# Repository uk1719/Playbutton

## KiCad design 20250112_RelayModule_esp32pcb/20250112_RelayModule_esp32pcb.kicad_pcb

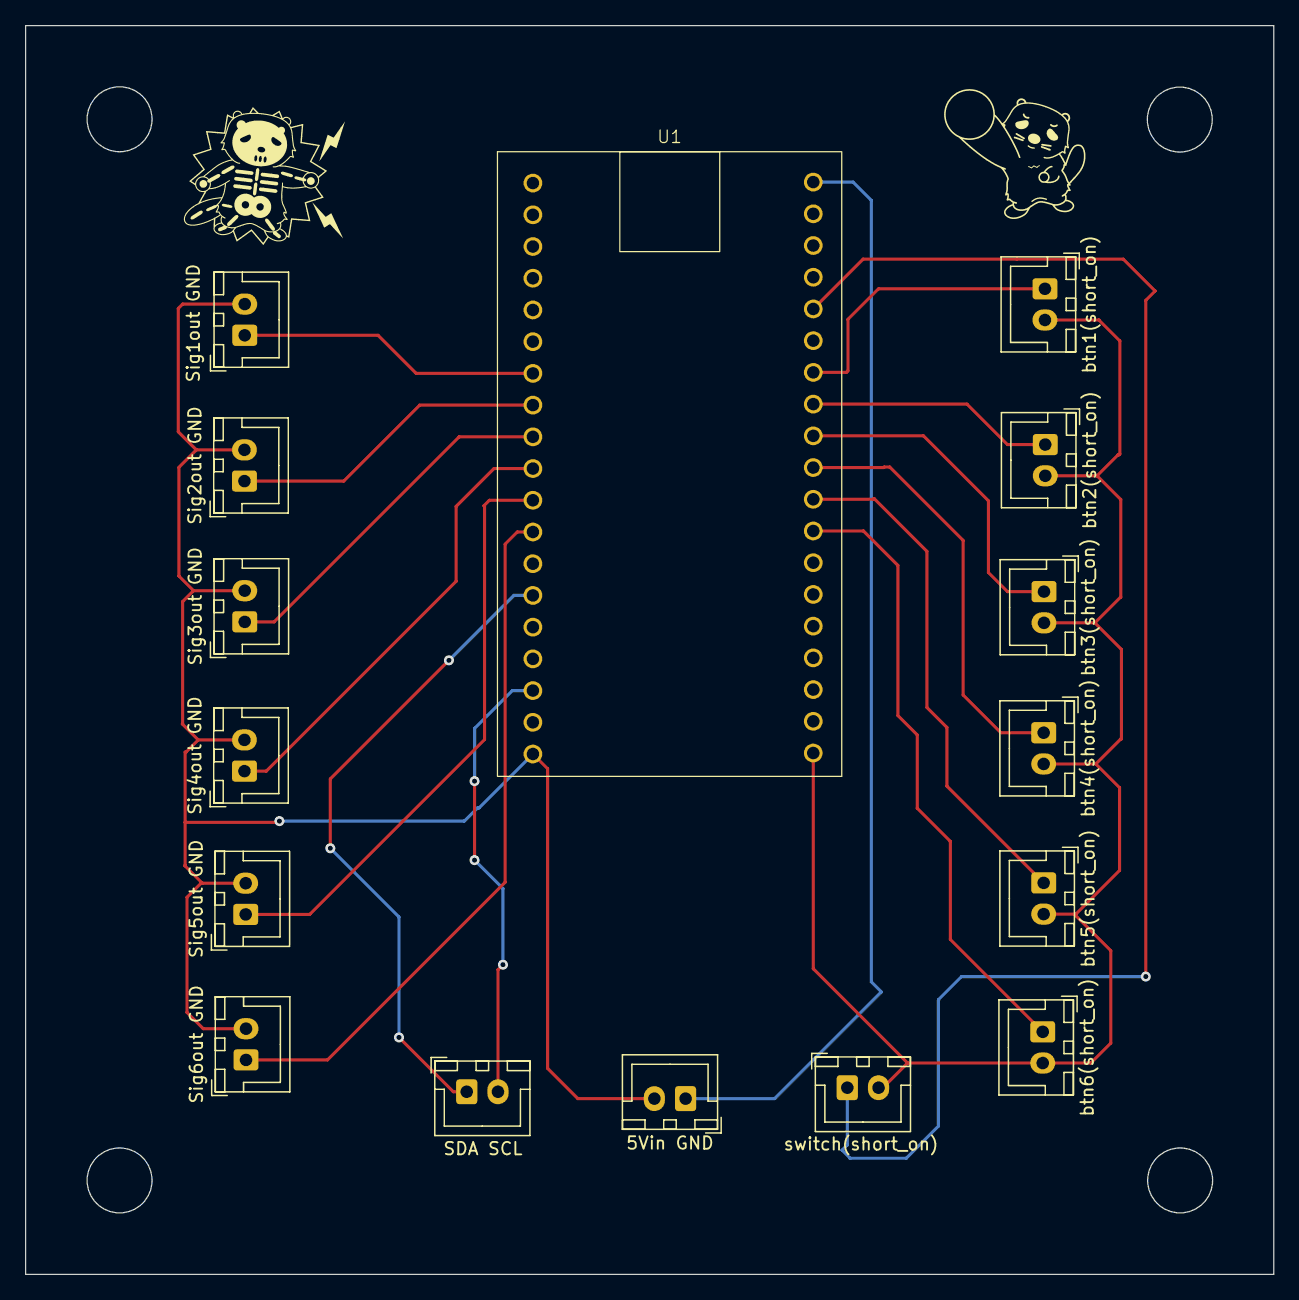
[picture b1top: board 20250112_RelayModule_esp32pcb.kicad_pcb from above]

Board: 2 copper layers, 99.9 x 100.0 mm, 16 parts (0 on the bottom side), 18 nets.

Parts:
5Vin GND: Conn_01x02_Pin; JST_XH_B2B-XH-A_1x02_P2.50mm_Vertical
SDA SCL: Conn_01x02_Pin; JST_XH_B2B-XH-A_1x02_P2.50mm_Vertical
Sig1out GND, Sig2out GND, Sig3out GND, Sig4out GND, Sig5out GND, Sig6out GND: Conn_01x02_Pin; JST_XH_B2B-XH-A_1x02_P2.50mm_Vertical
U1: ESP32-WROOM-32
btn1(short_on), btn2(short_on), btn3(short_on), btn4(short_on), btn5(short_on), btn6(short_on): Conn_01x02_Pin; JST_XH_B2B-XH-A_1x02_P2.50mm_Vertical
switch(short_on): Conn_01x02_Pin; JST_XH_B2B-XH-A_1x02_P2.50mm_Vertical

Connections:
unnamed: Sig1out GND.1, U1.7 (P4)
unnamed: 5Vin GND.2, Sig1out GND.2, Sig2out GND.2, Sig3out GND.2, Sig4out GND.2, Sig5out GND.2, Sig6out GND.2, U1.19 (GND)
unnamed: Sig2out GND.1, U1.8 (P16)
unnamed: Sig3out GND.1, U1.9 (P17)
unnamed: Sig4out GND.1, U1.10 (P5)
unnamed: Sig5out GND.1, U1.11 (P18)
unnamed: Sig6out GND.1, U1.12 (P19)
unnamed: U1.28 (P27), btn3(short_on).1
unnamed: U1.29 (P26), btn4(short_on).1
unnamed: U1.30 (P25), btn5(short_on).1
unnamed: U1.31 (P33), btn6(short_on).1
unnamed: U1.38 (3.3V), btn1(short_on).2, btn2(short_on).2, btn3(short_on).2, btn4(short_on).2, btn5(short_on).2, btn6(short_on).2, switch(short_on).2
unnamed: SDA SCL.1, U1.14 (P21)
unnamed: SDA SCL.2, U1.17 (P22)
unnamed: U1.24 (P13), switch(short_on).1
unnamed: 5Vin GND.1, U1.20 (5V)
unnamed: U1.26 (P12), btn1(short_on).1
unnamed: U1.27 (P14), btn2(short_on).1

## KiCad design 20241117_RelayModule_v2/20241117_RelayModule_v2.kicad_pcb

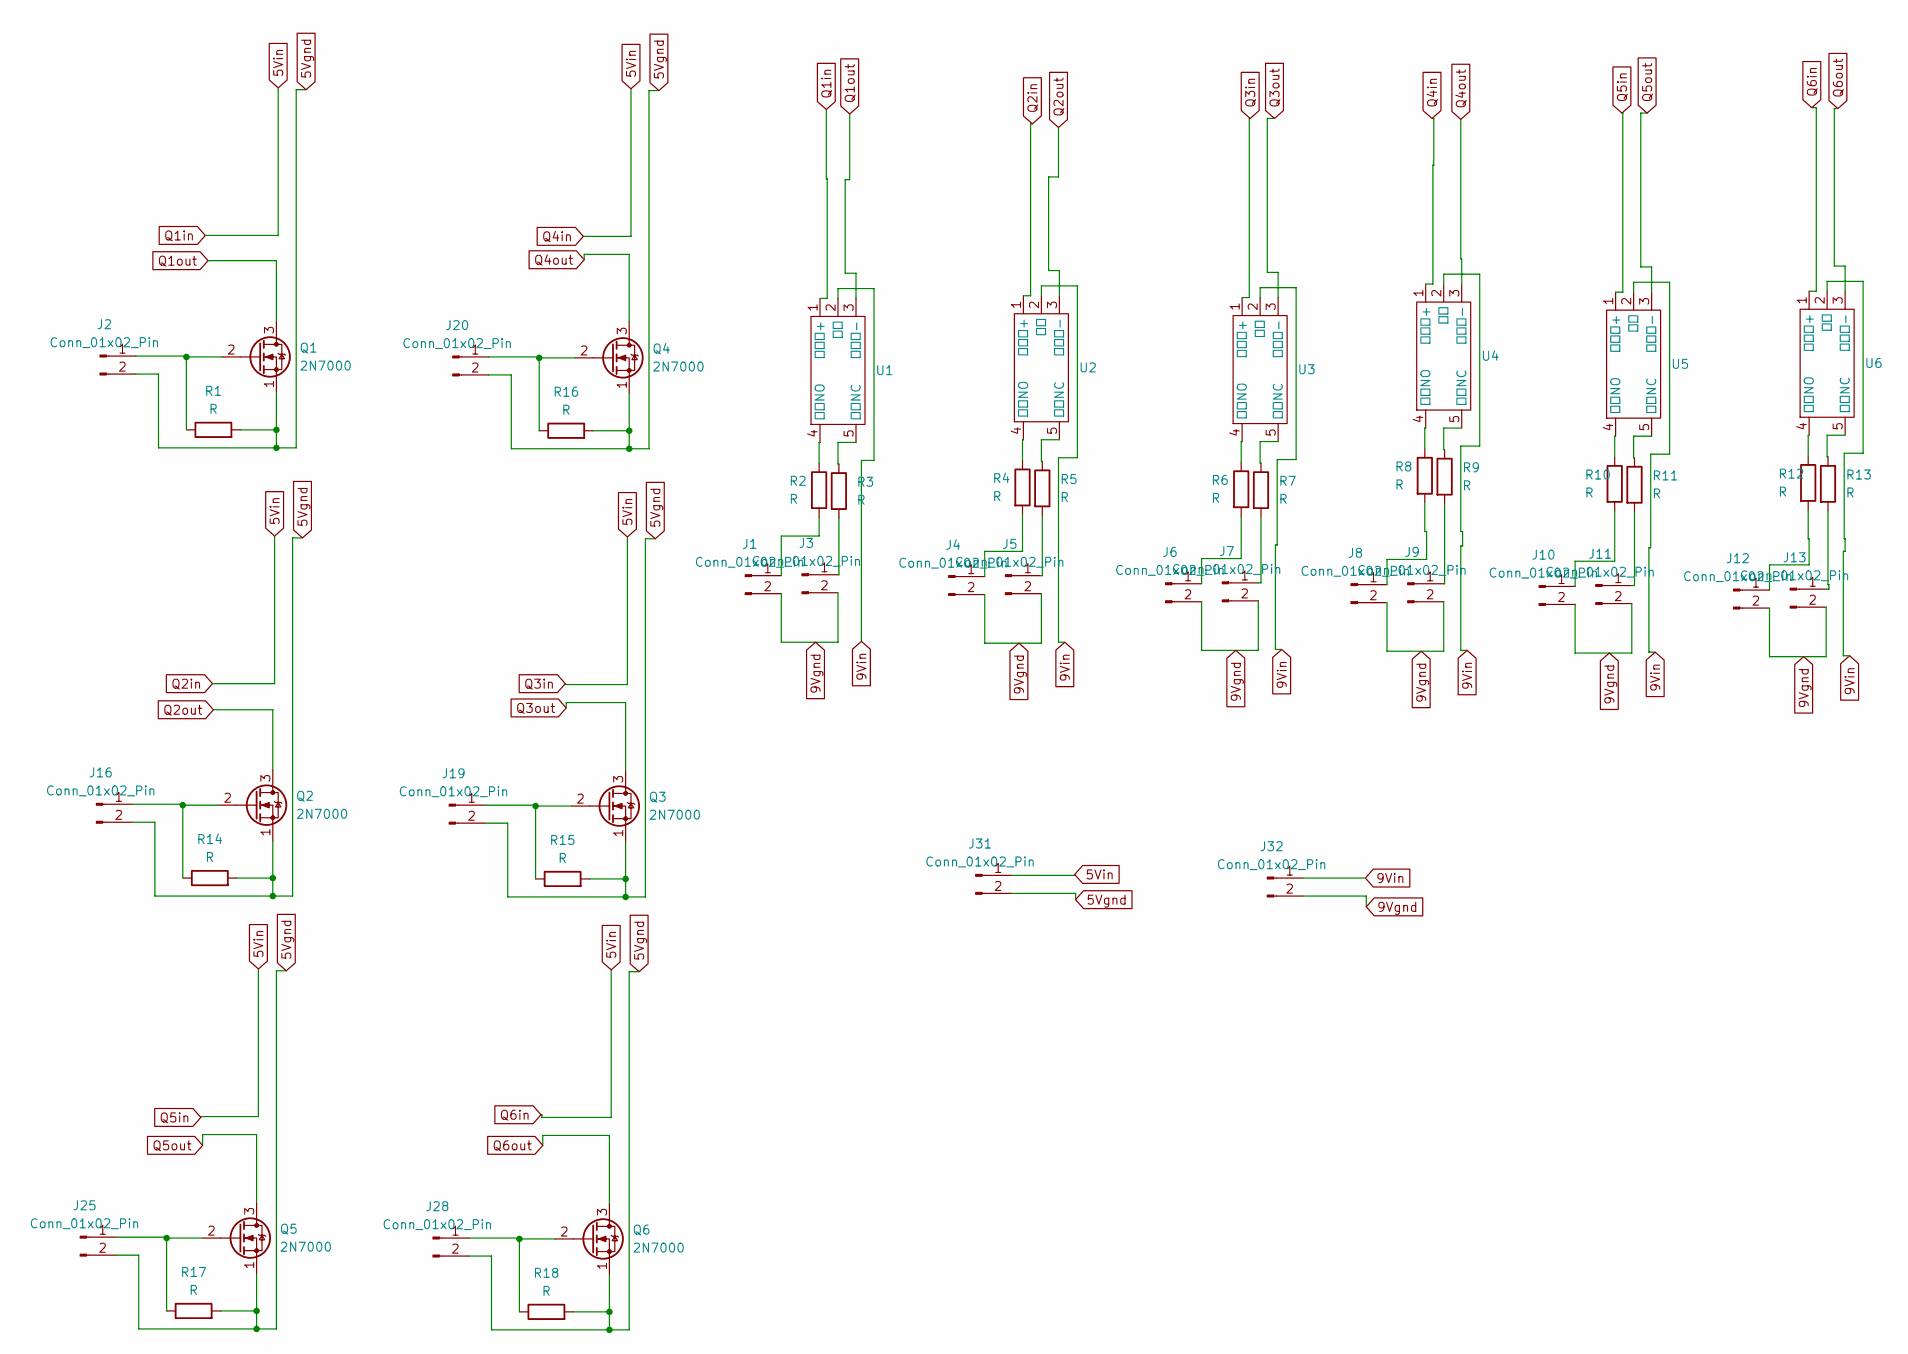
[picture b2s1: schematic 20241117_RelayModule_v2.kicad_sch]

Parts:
J1, J2, J3, J4, J5, J6, J7, J8, J9, J10, J11, J12, J13, J16, J19, J20, J25, J28, J31: Conn_01x02_Pin; JST_XH_B2B-XH-A_1x02_P2.50mm_Vertical
J32: Conn_01x02_Pin; JST_VH_B2P-VH_1x02_P3.96mm_Vertical
Q1, Q2, Q3, Q4, Q5, Q6: 2N7000; TO-92_Inline
R1, R2, R3, R4, R5, R6, R7, R8, R9, R10, R11, R12, R13, R14, R15, R16, R17, R18: R; R_Axial_DIN0309_L9.0mm_D3.2mm_P2.54mm_Vertical
U1, U2, U3, U4, U5, U6: RELAY_SRD-05VDC-SL-C

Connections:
5Vgnd: J2.2, J16.2, J19.2, J20.2, J25.2, J28.2, J31.2, Q1.1 (S), Q2.1 (S), Q3.1 (S), Q4.1 (S), Q5.1 (S), Q6.1 (S), R1.2, R14.2, R15.2, R16.2, R17.2, R18.2
5Vin: J31.1, U1.1 (コイル+), U2.1 (コイル+), U3.1 (コイル+), U4.1 (コイル+), U5.1 (コイル+), U6.1 (コイル+)
9Vgnd: J1.2, J3.2, J4.2, J5.2, J6.2, J7.2, J8.2, J9.2, J10.2, J11.2, J12.2, J13.2, J32.2
9Vin: J32.1, U1.2 (入力), U2.2 (入力), U3.2 (入力), U4.2 (入力), U5.2 (入力), U6.2 (入力)
unnamed: J1.1, R2.2
unnamed: J2.1, Q1.2 (G), R1.1
unnamed: J3.1, R3.2
unnamed: J4.1, R4.2
unnamed: J5.1, R5.2
unnamed: J6.1, R6.2
unnamed: J7.1, R7.2
unnamed: J8.1, R8.2
unnamed: J9.1, R9.2
unnamed: J10.1, R10.2
unnamed: J11.1, R11.2
unnamed: J12.1, R12.2
unnamed: J13.1, R13.2
unnamed: J16.1, Q2.2 (G), R14.1
unnamed: J19.1, Q3.2 (G), R15.1
unnamed: J20.1, Q4.2 (G), R16.1
unnamed: J25.1, Q5.2 (G), R17.1
unnamed: J28.1, Q6.2 (G), R18.1
unnamed: R3.1, U1.5 (出力NC)
unnamed: R2.1, U1.4 (出力NO)
unnamed: R5.1, U2.5 (出力NC)
unnamed: R4.1, U2.4 (出力NO)
unnamed: R7.1, U3.5 (出力NC)
unnamed: R6.1, U3.4 (出力NO)
unnamed: R9.1, U4.5 (出力NC)
unnamed: R8.1, U4.4 (出力NO)
unnamed: R11.1, U5.5 (出力NC)
unnamed: R10.1, U5.4 (出力NO)
unnamed: R13.1, U6.5 (出力NC)
unnamed: R12.1, U6.4 (出力NO)
Q1out: Q1.3 (D), U1.3 (コイル-)
Q2out: Q2.3 (D), U2.3 (コイル-)
Q3out: Q3.3 (D), U3.3 (コイル-)
Q4out: Q4.3 (D), U4.3 (コイル-)
Q5out: Q5.3 (D), U5.3 (コイル-)
Q6out: Q6.3 (D), U6.3 (コイル-)

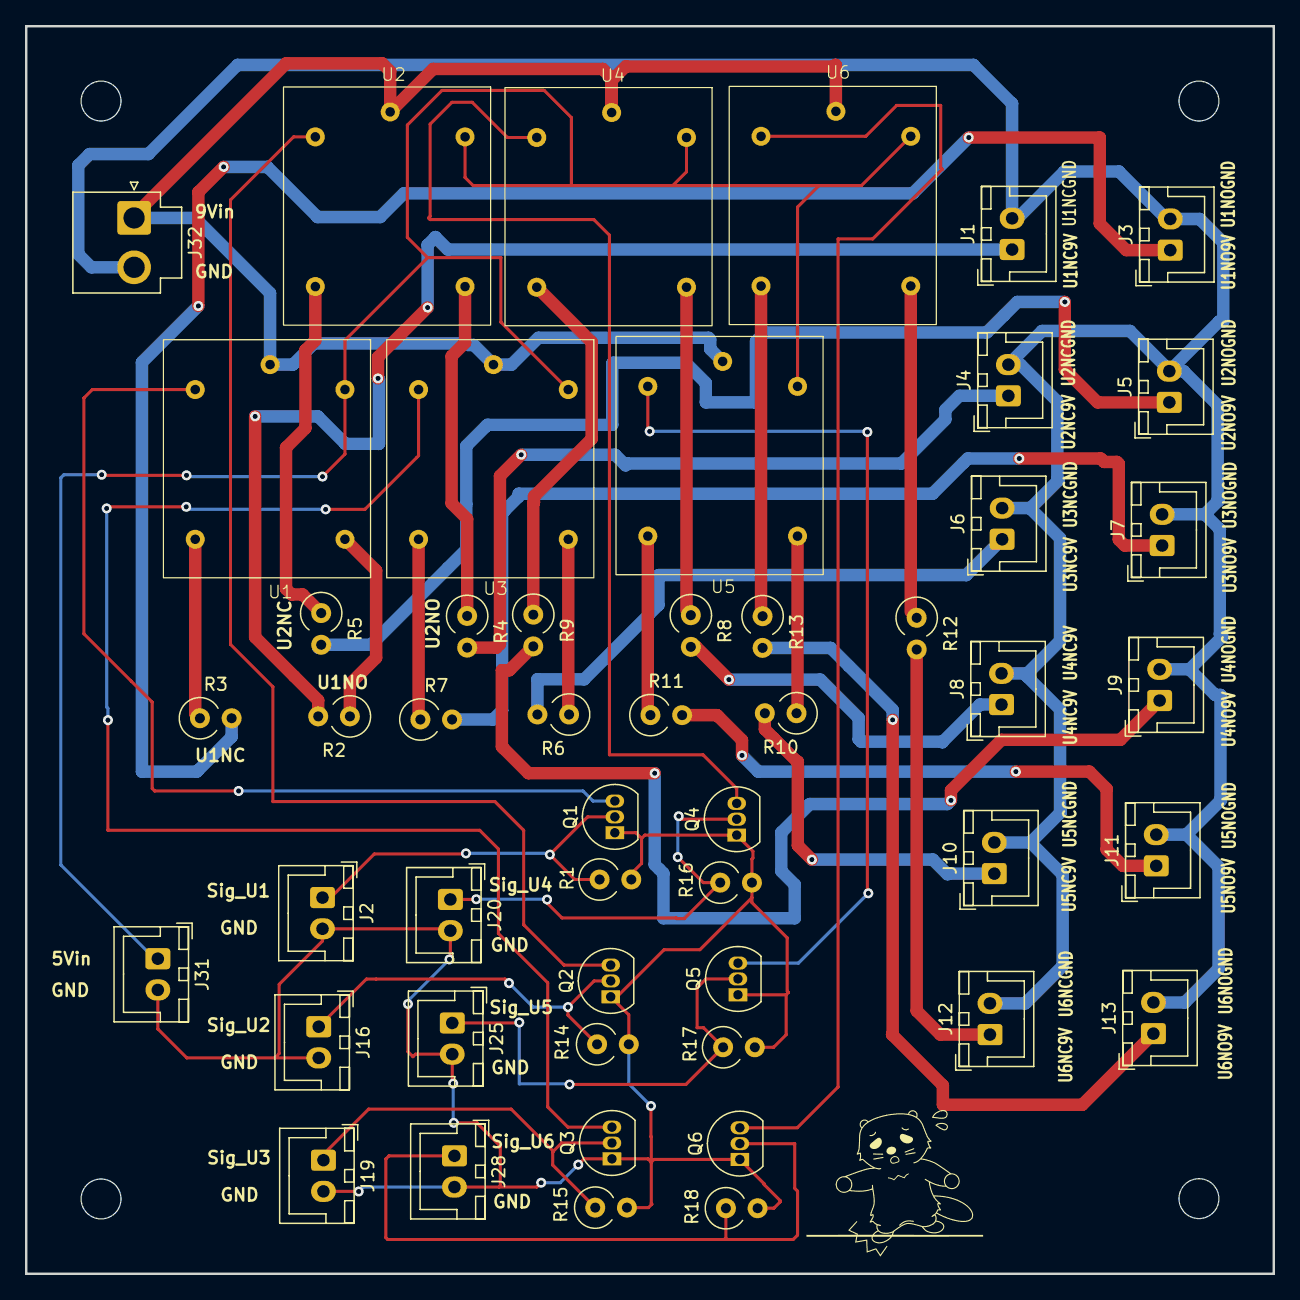
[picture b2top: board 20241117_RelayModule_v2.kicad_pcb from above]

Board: 2 copper layers, 100.0 x 100.0 mm, 50 parts (0 on the bottom side), 40 nets.

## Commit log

2025-08-29 リレーモジュールとesp32コントロール基板のkicadファイルを追加
2025-09-01 プログラムコード保存(全問正解のみ実装)
2025-09-13 正解時の動作修正
2025-10-05 Button_statusコード修正
